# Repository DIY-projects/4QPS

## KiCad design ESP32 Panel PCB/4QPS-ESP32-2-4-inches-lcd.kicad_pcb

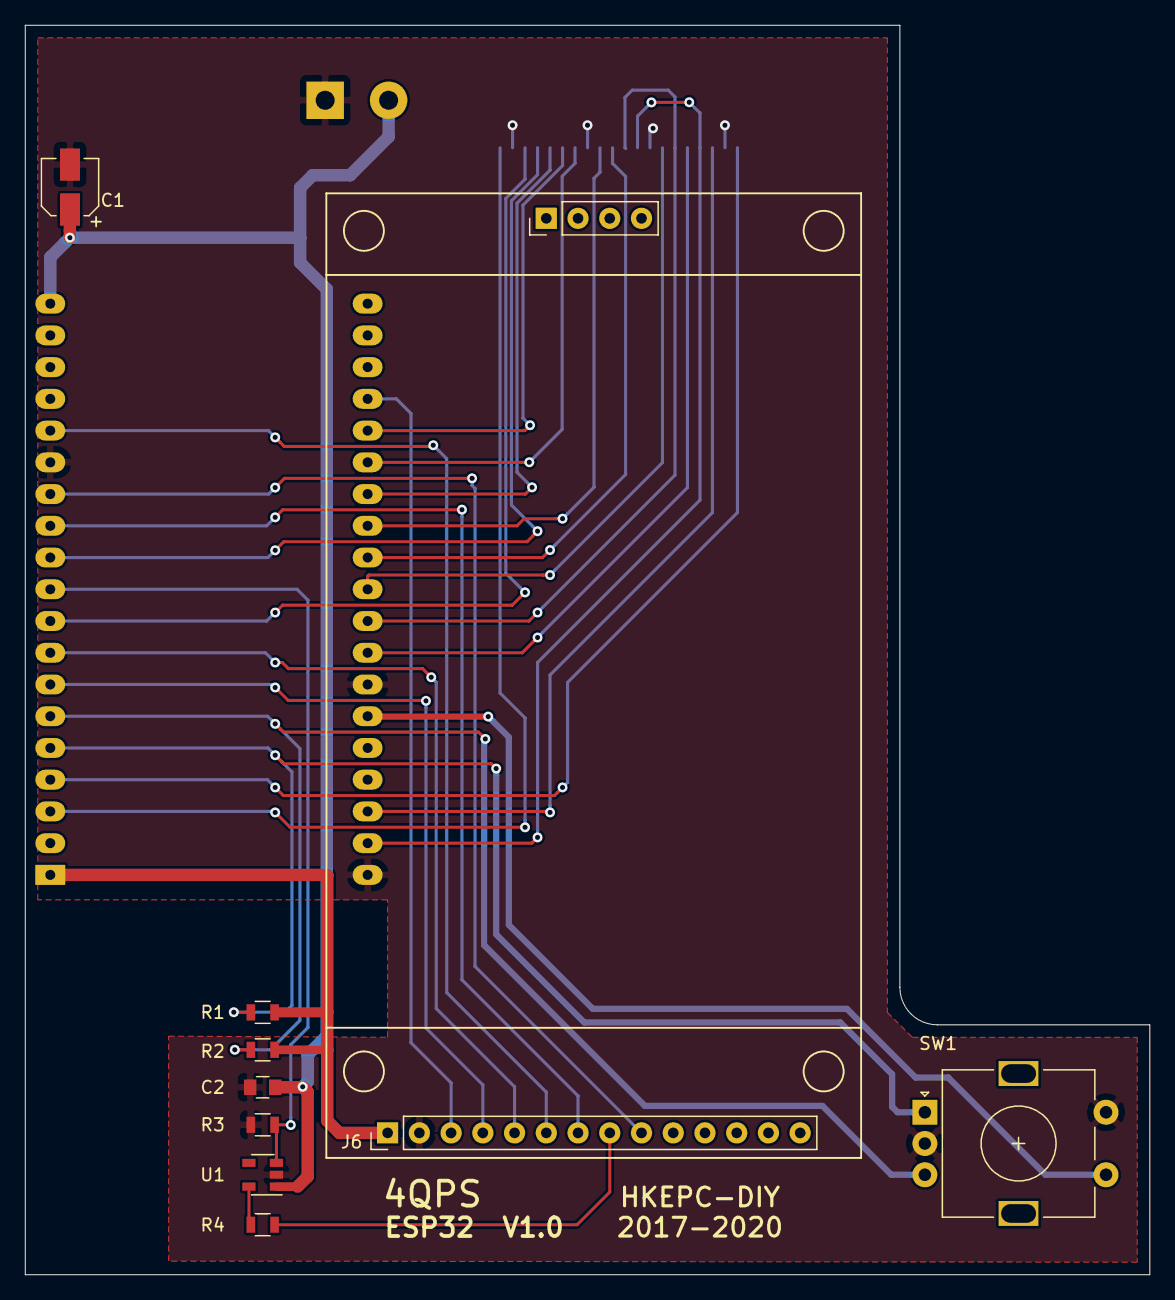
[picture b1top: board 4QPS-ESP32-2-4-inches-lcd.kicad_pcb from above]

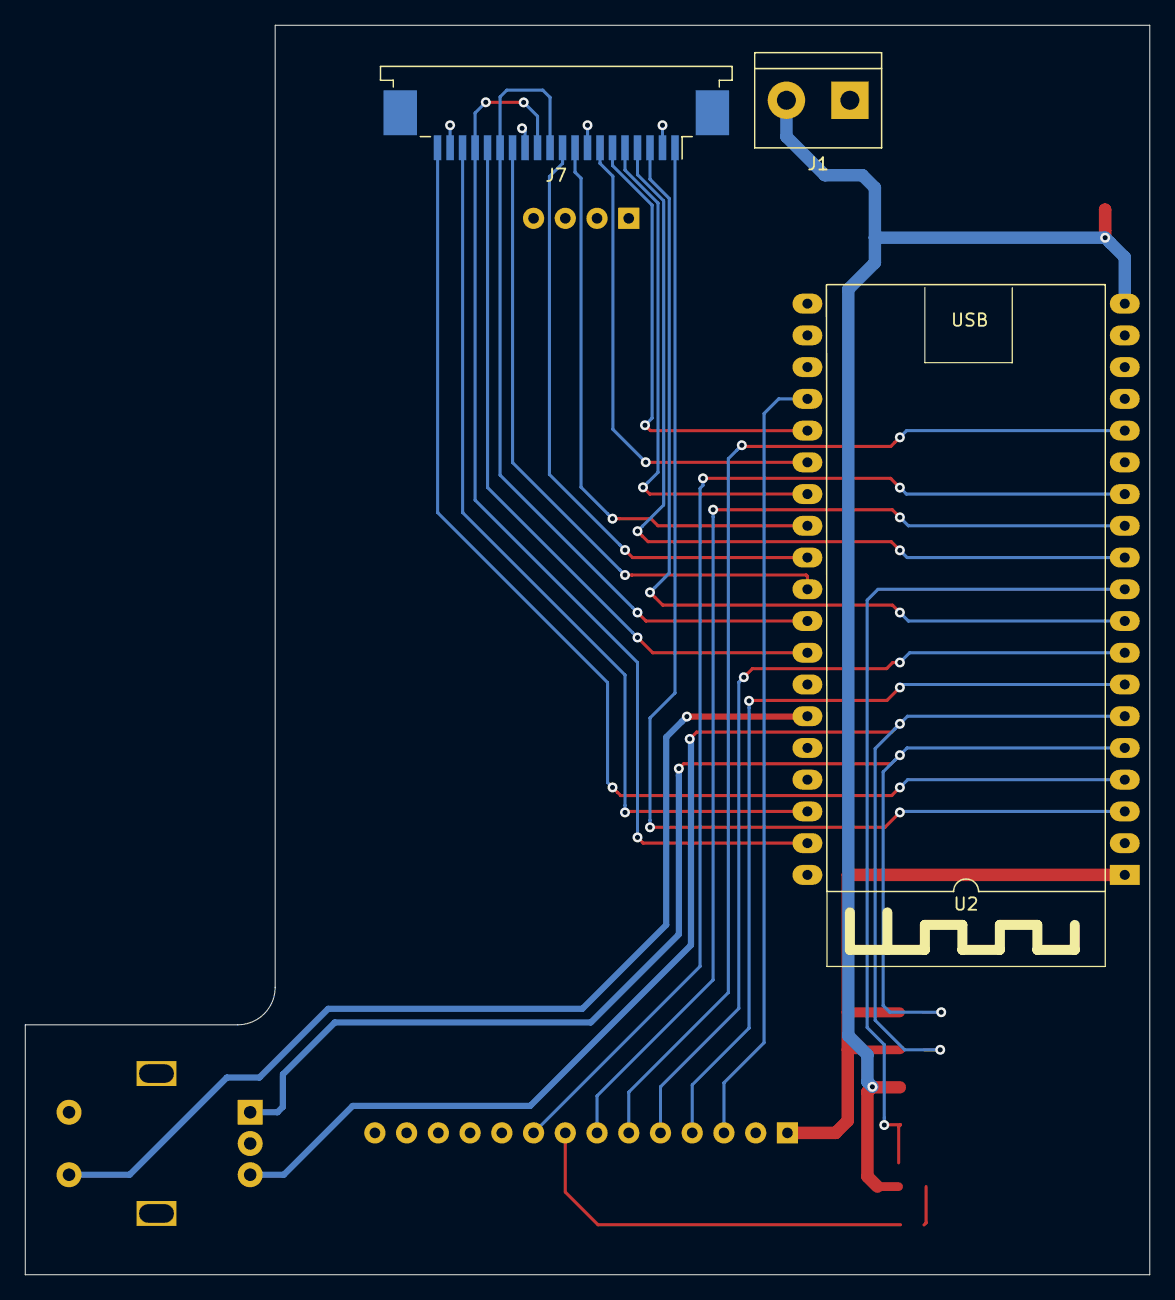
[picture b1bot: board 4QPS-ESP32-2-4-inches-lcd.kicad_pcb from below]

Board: 2 copper layers, 90.0 x 100.0 mm, 12 parts (3 on the bottom side), 29 nets.

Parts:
C1: CP1; CP_Elec_4x5.3
C2: C; C_0805
J1: Screw_Terminal_01x02; TerminalBlock_bornier-2_P5.08mm
J6: LCD-2-4-CONN; 2-4-inches-LCD
J7: 4QPS-CONN; TE_2-84952-0_1x20-1MP_P1.0mm_Horizontal
R1, R2, R3, R4: R_Small; R_0805
SW1: Rotary_Encoder_Switch; RotaryEncoder_Alps_EC11E-Switch_Vertical_H20mm
U1: TLV73333PDBV; SOT-23-5
U2: ESP32-DEV-BOARD; ESP32-DEVKIT-V4

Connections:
+3V3: J6.1, R1.1, R2.2, U2.1
+5V: C1.1, C2.1, J1.2, U1.1, U2.19
BL: R4.1, U1.5
BL_CTRL: R3.2, U1.3, U2.10
ENC_A: R1.2, SW1.A, U2.5
ENC_B: R2.1, SW1.B, U2.6
GND: C1.2, C2.2, J1.1, J6.2, J7.2, J7.8, J7.13, J7.19, R3.1, SW1.C, SW1.S2, U1.2, U2.14, U2.32, U2.38
unnamed: J6.3, U2.23
unnamed: J6.4, U2.7
unnamed: J6.5, U2.8
unnamed: J6.6, U2.15
unnamed: J6.7, U2.12
unnamed: J6.8, R4.2
unnamed: J6.9, U2.13
unnamed: J7.3, U2.9
unnamed: J7.4, U2.11
unnamed: J7.5, U2.26
unnamed: J7.6, U2.24
unnamed: J7.7, U2.25
unnamed: J7.9, U2.27
unnamed: J7.10, U2.28
unnamed: J7.11, J7.15, U2.30
unnamed: J7.12, J7.17, U2.37
unnamed: J7.14, U2.29
unnamed: J7.16, U2.31
unnamed: J7.18, U2.36
PB: SW1.S1, U2.33
T1: J7.1, U2.3
T2: J7.20, U2.4

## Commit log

2021-12-12 Secod Commit
2021-12-12 Commit 3
